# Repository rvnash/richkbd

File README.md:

# richkbd 2.0
 
The richkbd keyboard is a 42 key single piece Kaihl Choc Hotswap based keyboard which uses the [RP2040](https://www.raspberrypi.com/products/rp2040/) microcontroller. The layout of the keys is identical to two [Corne keyboards](https://github.com/foostan/crkbd) joined together into one. The halves are placed 21° from horizontal and the top keys are separated by 35mm.

If you wanted to construct your own, take a look at the [Build Guide](doc/buildguide.md).

## Features

- Powered by the [RP2040 Stamp](https://www.solder.party/docs/rp2040-stamp) helper board
- USB-C Card edge connector
- Neopixel LED per key
- OLED Display
- Buttons to reset and enter bootloader mode
- Fairly thin with a bottom plate, PCB board layer, and a top layer to hold the sockets
 
## Software

There is a full QMK software implementation which you can find [here](https://github.com/rvnash/qmk_firmware/tree/rvnash_rp2040/keyboards/rvnash/richkbd). If you don't enjoy working from the source, you can find a released flashable version [here](https://github.com/rvnash/qmk_firmware/releases).

## Photos

Here is a completed keyboard with a random selection of keycaps on.

Side View

The raw PCB

A soldered PCB

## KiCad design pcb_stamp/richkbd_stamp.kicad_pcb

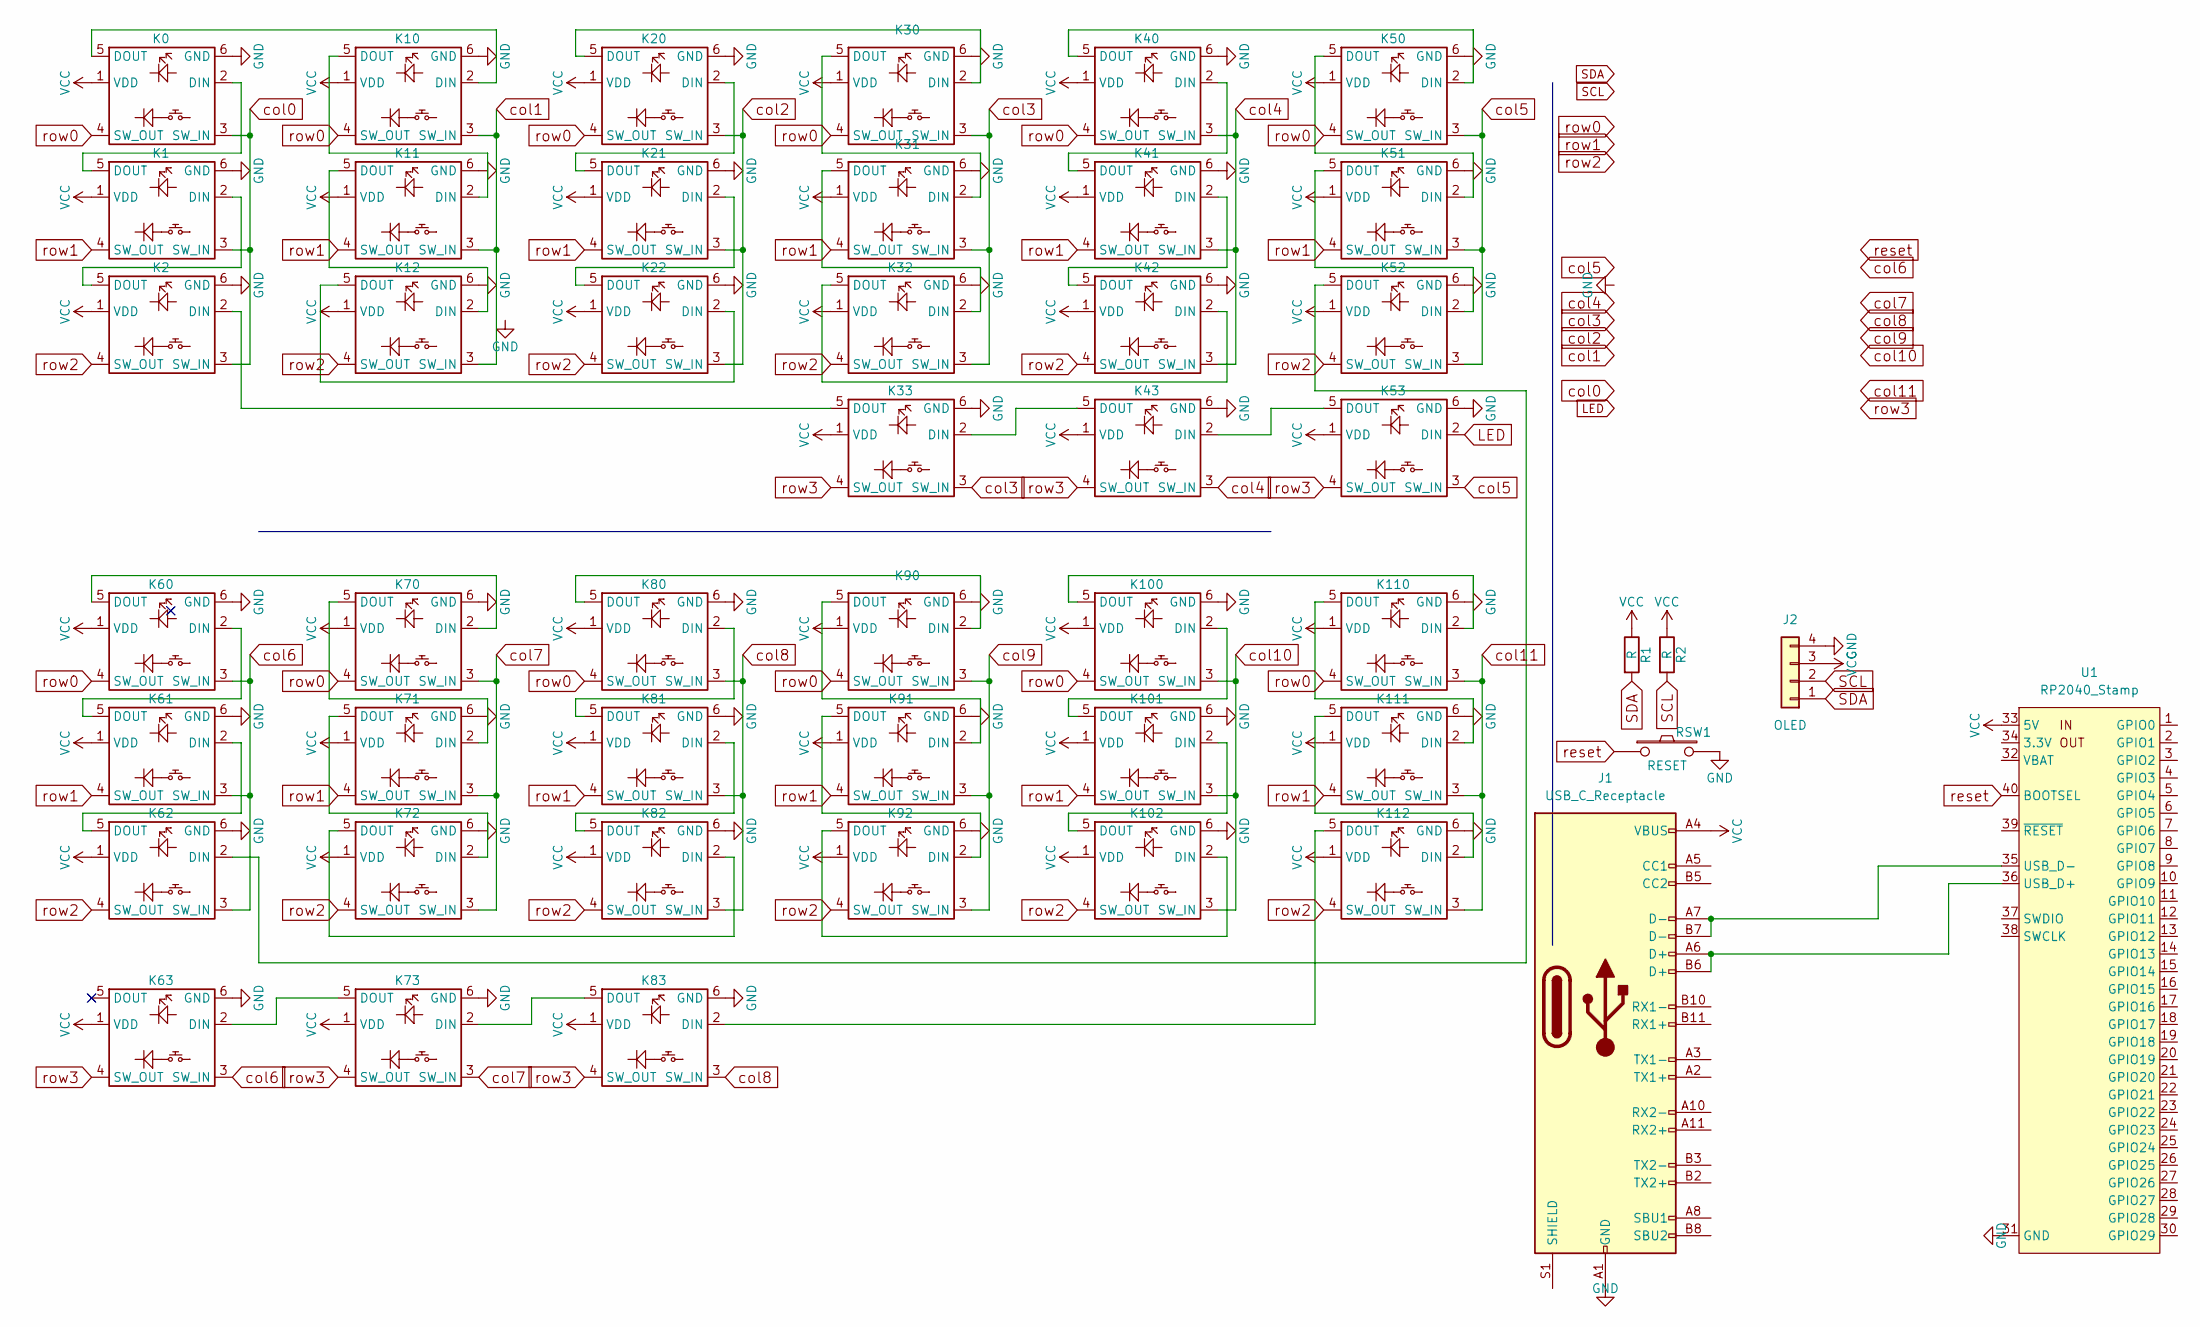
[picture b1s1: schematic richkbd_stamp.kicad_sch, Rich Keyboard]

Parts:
J1: USB_C_Receptacle
J2: OLED
K0, K1, K2, K10, K11, K12, K20, K21, K22, K30, K31, K32, K33, K40, K41, K42, K43, K50, K51, K52, K53, K60, K61, K62, K63, K70, K71, K72, K73, K80, K81, K82, K83, K90, K91, K92, K100, K101, K102, K110, K111, K112: key-diode-led; key_diode_led
R1, R2: R
RSW1: RESET; ResetSW
U1: RP2040_Stamp; RP2040_Stamp_SMD

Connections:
GND: J1.A1 (GND), J1.A12 (GND), J1.B1 (GND), J1.B12 (GND), J2.4, K0.6 (GND), K1.6 (GND), K2.6 (GND), K10.6 (GND), K11.6 (GND), K12.6 (GND), K20.6 (GND), K21.6 (GND), K22.6 (GND), K30.6 (GND), K31.6 (GND), K32.6 (GND), K33.6 (GND), K40.6 (GND), K41.6 (GND), K42.6 (GND), K43.6 (GND), K50.6 (GND), K51.6 (GND), K52.6 (GND), K53.6 (GND), K60.6 (GND), K61.6 (GND), K62.6 (GND), K63.6 (GND), K70.6 (GND), K71.6 (GND), K72.6 (GND), K73.6 (GND), K80.6 (GND), K81.6 (GND), K82.6 (GND), K83.6 (GND), K90.6 (GND), K91.6 (GND), K92.6 (GND), K100.6 (GND), K101.6 (GND), K102.6 (GND), K110.6 (GND), K111.6 (GND), K112.6 (GND), RSW1.2, U1.31 (GND)
LED: K53.2 (DIN)
unnamed: J1.A6 (D+), J1.B6 (D+), U1.36 (USB_D+)
unnamed: J1.A7 (D-), J1.B7 (D-), U1.35 (USB_D-)
unnamed: K0.2 (DIN), K1.5 (DOUT)
unnamed: K0.5 (DOUT), K10.2 (DIN)
unnamed: K1.2 (DIN), K2.5 (DOUT)
unnamed: K2.2 (DIN), K33.5 (DOUT)
unnamed: K10.5 (DOUT), K11.2 (DIN)
unnamed: K11.5 (DOUT), K12.2 (DIN)
unnamed: K12.5 (DOUT), K22.2 (DIN)
unnamed: K20.2 (DIN), K21.5 (DOUT)
unnamed: K20.5 (DOUT), K30.2 (DIN)
unnamed: K21.2 (DIN), K22.5 (DOUT)
unnamed: K30.5 (DOUT), K31.2 (DIN)
unnamed: K31.5 (DOUT), K32.2 (DIN)
unnamed: K32.5 (DOUT), K42.2 (DIN)
unnamed: K33.2 (DIN), K43.5 (DOUT)
unnamed: K40.2 (DIN), K41.5 (DOUT)
unnamed: K40.5 (DOUT), K50.2 (DIN)
unnamed: K41.2 (DIN), K42.5 (DOUT)
unnamed: K43.2 (DIN), K53.5 (DOUT)
unnamed: K50.5 (DOUT), K51.2 (DIN)
unnamed: K51.5 (DOUT), K52.2 (DIN)
unnamed: K52.5 (DOUT), K62.2 (DIN)
unnamed: K60.2 (DIN), K61.5 (DOUT)
unnamed: K60.5 (DOUT), K70.2 (DIN)
unnamed: K61.2 (DIN), K62.5 (DOUT)
unnamed: K63.2 (DIN), K73.5 (DOUT)
unnamed: K70.5 (DOUT), K71.2 (DIN)
unnamed: K71.5 (DOUT), K72.2 (DIN)
unnamed: K72.5 (DOUT), K82.2 (DIN)
unnamed: K73.2 (DIN), K83.5 (DOUT)
unnamed: K80.2 (DIN), K81.5 (DOUT)
unnamed: K80.5 (DOUT), K90.2 (DIN)
unnamed: K81.2 (DIN), K82.5 (DOUT)
unnamed: K90.5 (DOUT), K91.2 (DIN)
unnamed: K91.5 (DOUT), K92.2 (DIN)
unnamed: K100.2 (DIN), K101.5 (DOUT)
unnamed: K100.5 (DOUT), K110.2 (DIN)
unnamed: K101.2 (DIN), K102.5 (DOUT)
unnamed: K92.5 (DOUT), K102.2 (DIN)
unnamed: K110.5 (DOUT), K111.2 (DIN)
unnamed: K111.5 (DOUT), K112.2 (DIN)
unnamed: K83.2 (DIN), K112.5 (DOUT)
SCL: J2.2, R2.2
SDA: J2.1, R1.2
VCC: J1.A4 (VBUS), J1.A9 (VBUS), J1.B4 (VBUS), J1.B9 (VBUS), J2.3, K0.1 (VDD), K1.1 (VDD), K2.1 (VDD), K10.1 (VDD), K11.1 (VDD), K12.1 (VDD), K20.1 (VDD), K21.1 (VDD), K22.1 (VDD), K30.1 (VDD), K31.1 (VDD), K32.1 (VDD), K33.1 (VDD), K40.1 (VDD), K41.1 (VDD), K42.1 (VDD), K43.1 (VDD), K50.1 (VDD), K51.1 (VDD), K52.1 (VDD), K53.1 (VDD), K60.1 (VDD), K61.1 (VDD), K62.1 (VDD), K63.1 (VDD), K70.1 (VDD), K71.1 (VDD), K72.1 (VDD), K73.1 (VDD), K80.1 (VDD), K81.1 (VDD), K82.1 (VDD), K83.1 (VDD), K90.1 (VDD), K91.1 (VDD), K92.1 (VDD), K100.1 (VDD), K101.1 (VDD), K102.1 (VDD), K110.1 (VDD), K111.1 (VDD), K112.1 (VDD), R1.1, R2.1, U1.33 (5V)
col0: K0.3 (SW_IN), K1.3 (SW_IN), K2.3 (SW_IN)
col1: K10.3 (SW_IN), K11.3 (SW_IN), K12.3 (SW_IN)
col2: K20.3 (SW_IN), K21.3 (SW_IN), K22.3 (SW_IN)
col3: K30.3 (SW_IN), K31.3 (SW_IN), K32.3 (SW_IN), K33.3 (SW_IN)
col4: K40.3 (SW_IN), K41.3 (SW_IN), K42.3 (SW_IN), K43.3 (SW_IN)
col5: K50.3 (SW_IN), K51.3 (SW_IN), K52.3 (SW_IN), K53.3 (SW_IN)
col6: K60.3 (SW_IN), K61.3 (SW_IN), K62.3 (SW_IN), K63.3 (SW_IN)
col7: K70.3 (SW_IN), K71.3 (SW_IN), K72.3 (SW_IN), K73.3 (SW_IN)
col8: K80.3 (SW_IN), K81.3 (SW_IN), K82.3 (SW_IN), K83.3 (SW_IN)
col9: K90.3 (SW_IN), K91.3 (SW_IN), K92.3 (SW_IN)
col10: K100.3 (SW_IN), K101.3 (SW_IN), K102.3 (SW_IN)
col11: K110.3 (SW_IN), K111.3 (SW_IN), K112.3 (SW_IN)
reset: RSW1.1, U1.40 (BOOTSEL)
row0: K0.4 (SW_OUT), K10.4 (SW_OUT), K20.4 (SW_OUT), K30.4 (SW_OUT), K40.4 (SW_OUT), K50.4 (SW_OUT), K60.4 (SW_OUT), K70.4 (SW_OUT), K80.4 (SW_OUT), K90.4 (SW_OUT), K100.4 (SW_OUT), K110.4 (SW_OUT)
row1: K1.4 (SW_OUT), K11.4 (SW_OUT), K21.4 (SW_OUT), K31.4 (SW_OUT), K41.4 (SW_OUT), K51.4 (SW_OUT), K61.4 (SW_OUT), K71.4 (SW_OUT), K81.4 (SW_OUT), K91.4 (SW_OUT), K101.4 (SW_OUT), K111.4 (SW_OUT)
row2: K2.4 (SW_OUT), K12.4 (SW_OUT), K22.4 (SW_OUT), K32.4 (SW_OUT), K42.4 (SW_OUT), K52.4 (SW_OUT), K62.4 (SW_OUT), K72.4 (SW_OUT), K82.4 (SW_OUT), K92.4 (SW_OUT), K102.4 (SW_OUT), K112.4 (SW_OUT)
row3: K33.4 (SW_OUT), K43.4 (SW_OUT), K53.4 (SW_OUT), K63.4 (SW_OUT), K73.4 (SW_OUT), K83.4 (SW_OUT)

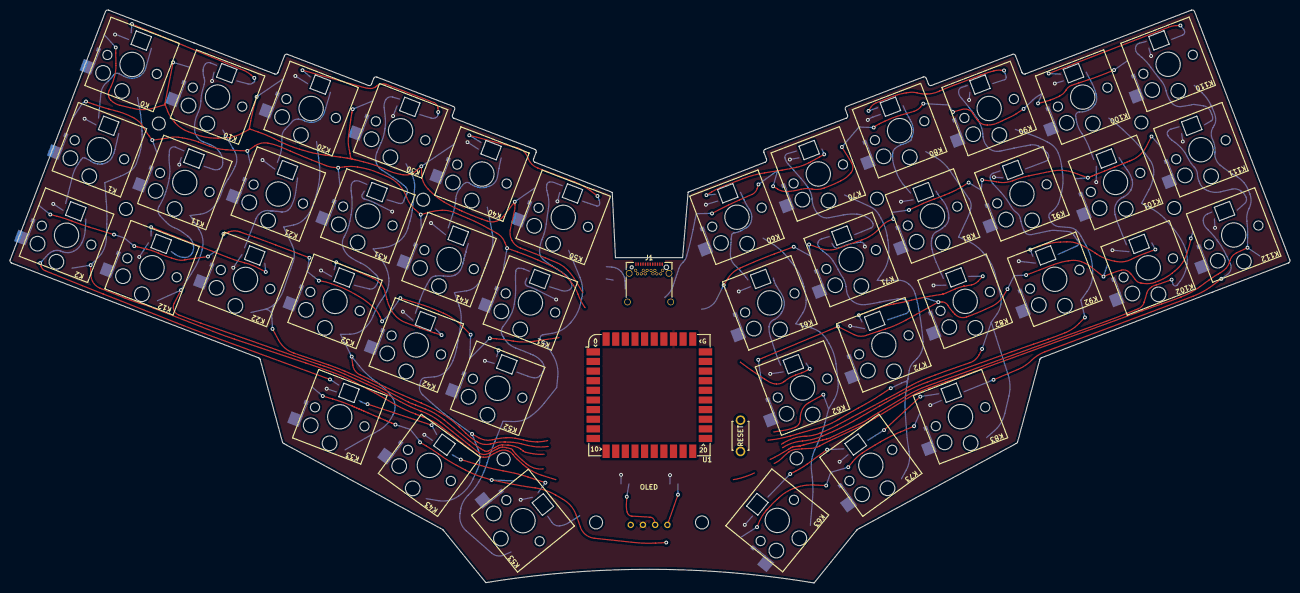
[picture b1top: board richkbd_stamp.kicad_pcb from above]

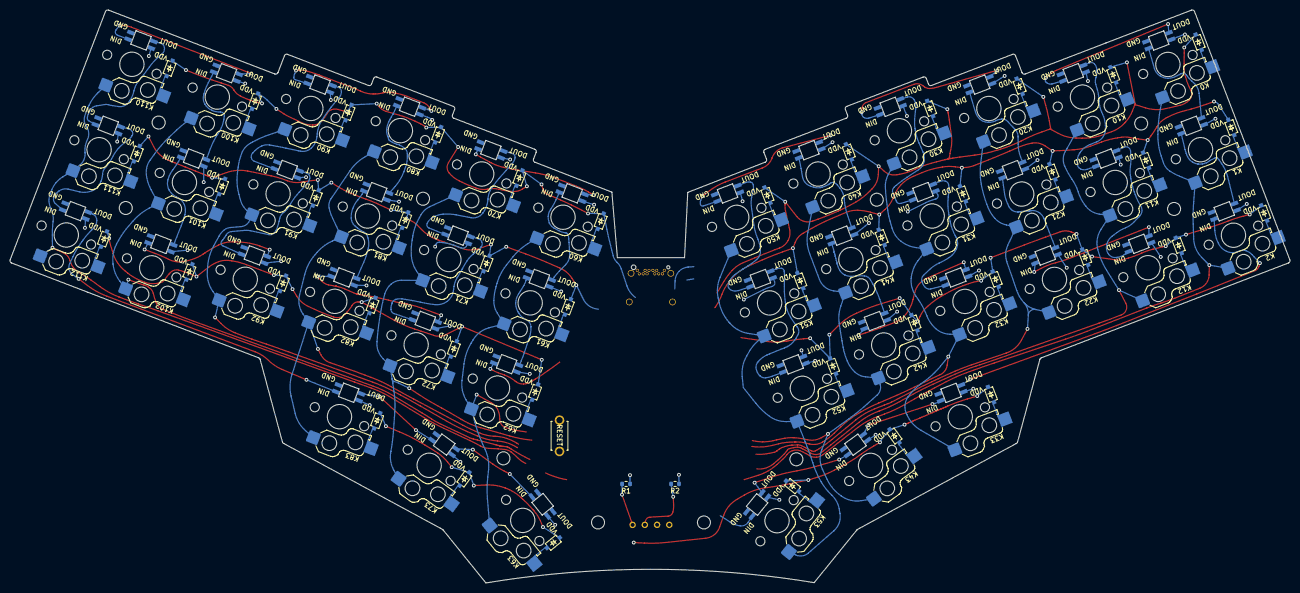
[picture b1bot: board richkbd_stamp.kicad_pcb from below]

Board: 2 copper layers, 265.9 x 119.0 mm, 48 parts (2 on the bottom side), 64 nets.

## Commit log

2022-09-01 Initialize with very incomplete schematic
2022-09-01 Completed 2 columns of switches and improved symmetry
2022-09-01 Completed schematic, but need to decide on rp2040 or not
2022-09-02 Start of board layout
2022-09-03 switches laid
2022-09-12 Left side routed
2022-09-12 Added a few more traces
2022-09-13 Finished routing and added start at stamp version
2022-09-15 Finished stamp routing
2022-09-15 Moved OLED up and fixed pin orientation
2022-09-15 Sent off for fab at JLC PCB
2022-09-18 Connected row3
2022-09-19 Start of rev2
    Moved stamp to back
2022-09-20 Put stamp on the bottom layer
2022-09-27 New layout for update to footprint of the neopixen
2022-09-28 Added diode on first LED pixel power pin to bring it into spec for the rp2040's 3.3V logic
2022-09-28 Changed the diode footprint for first one
2022-09-28 Minor tweaks.
2022-09-28 V2.0.0 Sent to JLCPCB for fab.
2022-09-29 Clean up some traces.
2022-10-15 Updated resistor values and moved lightsabres
2022-10-18 Started build guide
2022-10-18 A good start at the documentation.
2022-10-18 Clean up the build guide.
2022-10-18 Fix links to gerber files
2022-10-19 Readme mods
2022-10-19 Added pictures to readme and build guide
2022-10-19 Improved buildguide
2022-10-19 Fixed typo
2022-10-22 Made LED holes slightly larger
